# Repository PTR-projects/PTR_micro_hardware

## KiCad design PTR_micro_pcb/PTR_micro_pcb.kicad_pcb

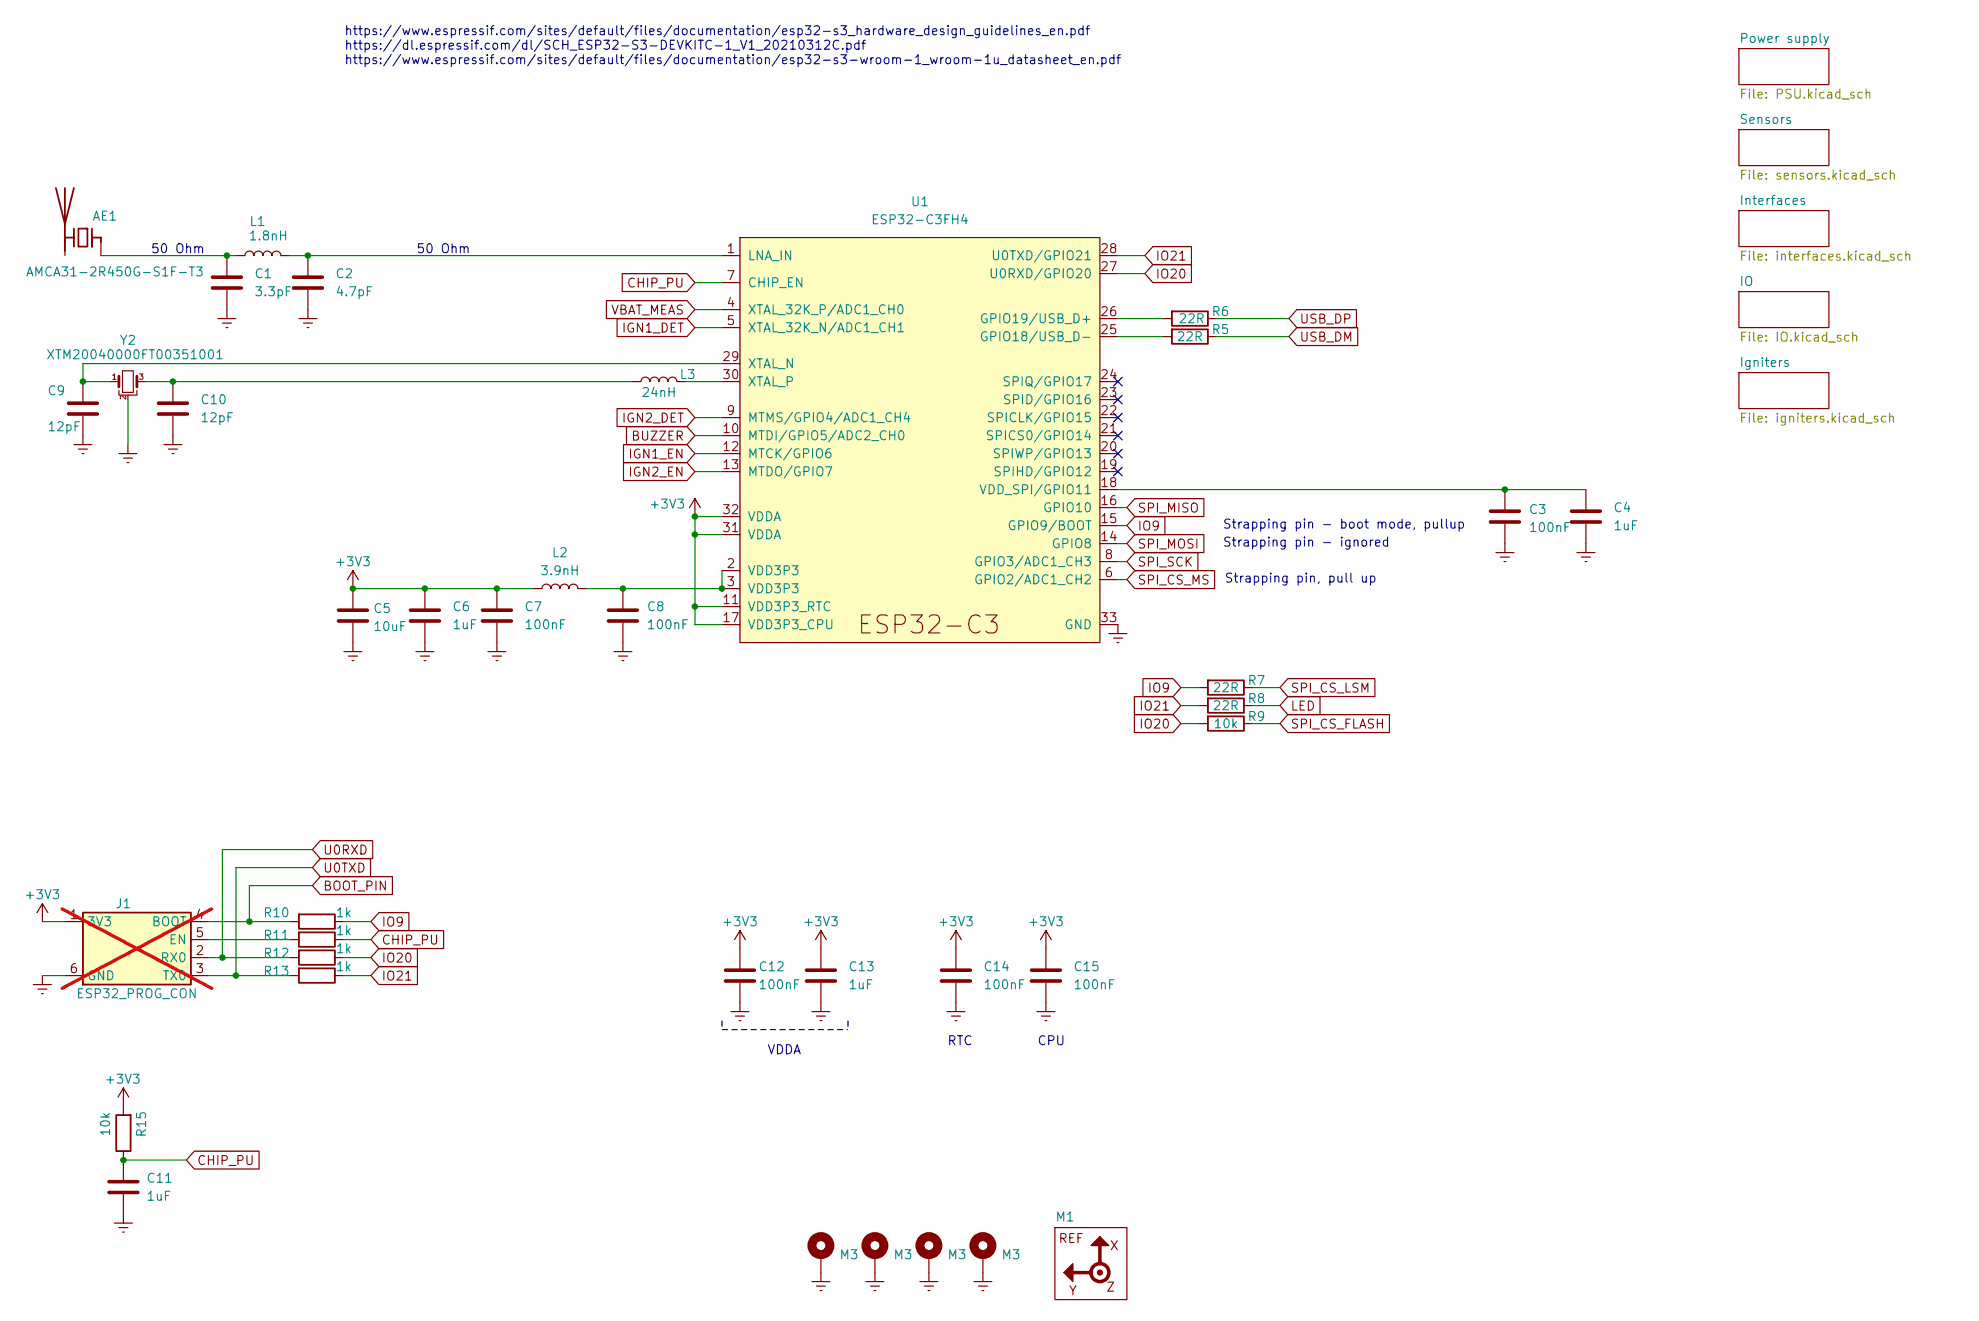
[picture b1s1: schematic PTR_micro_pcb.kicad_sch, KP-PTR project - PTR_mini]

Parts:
AE1: AMCA31-2R450G-S1F-T3
C1: 3.3pF; C_0402_1005Metric
C2: 4.7pF; C_0402_1005Metric
C3, C7, C8, C12, C14, C15: 100nF; C_0402_1005Metric
C4, C6, C11, C13: 1uF; C_0402_1005Metric
C5: 10uF; C_0603_1608Metric
C9, C10: 12pF; C_0402_1005Metric
H1, H2, H3, H4: M3; MountingHole_3.2mm_M3_DIN965_Pad
J1: ESP32_PROG_CON; PinHeader_1x06_P1.27mm_Vertical; not fitted
L1: 1.8nH; L_0402_1005Metric
L2: 3.9nH; L_0402_1005Metric
L3: 24nH; L_0402_1005Metric
M1: Reference_frame
R5, R6, R7, R8: 22R; R_0402_1005Metric
R9, R15: 10k; R_0402_1005Metric
R10, R11, R12, R13: 1k; R_0402_1005Metric
U1: ESP32-C3FH4; QFN-32-1EP_5x5mm_P0.5mm_EP3.45x3.45mm
Y2: XTM20040000FT00351001; Crystal_SMD_2016-4Pin_2.0x1.6mm

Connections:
+3V3: C5.1, C6.1, C7.1, C12.1, C13.1, C14.1, C15.1, J1.1 (3V3), L2.1, R15.2, U1.11 (VDD3P3_RTC), U1.17 (VDD3P3_CPU), U1.31 (VDDA), U1.32 (VDDA); also elsewhere on the board
BOOT_PIN: J1.4 (BOOT), R10.2
BUZZER: U1.10 (MTDI/GPIO5/ADC2_CH0); also elsewhere on the board
CHIP_PU: C11.2, R11.1, R15.1, U1.7 (CHIP_EN)
Earth: C1.2, C2.2, C3.2, C4.2, C5.2, C6.2, C7.2, C8.2, C9.1, C10.2, C11.1, C12.2, C13.2, C14.2, C15.2, H1.1 (1_1), H2.1 (1_1), H3.1 (1_1), H4.1 (1_1), J1.6 (GND), U1.33 (GND), Y2.2, Y2.4; also elsewhere on the board
IGN1_DET: U1.5 (XTAL_32K_N/ADC1_CH1); also elsewhere on the board
IGN1_EN: U1.12 (MTCK/GPIO6); also elsewhere on the board
IGN2_DET: U1.9 (MTMS/GPIO4/ADC1_CH4); also elsewhere on the board
IGN2_EN: U1.13 (MTDO/GPIO7); also elsewhere on the board
IO9: R7.2, R10.1, U1.15 (GPIO9/BOOT)
IO20: R9.2, R12.1, U1.27 (U0RXD/GPIO20)
IO21: R8.2, R13.1, U1.28 (U0TXD/GPIO21)
LED: R8.1; also elsewhere on the board
unnamed: AE1.1 (FEED_1), C1.1, L1.1
unnamed: C8.1, L2.2, U1.2 (VDD3P3), U1.3 (VDD3P3)
unnamed: C10.1, L3.1, Y2.3
unnamed: J1.5 (EN), R11.2
unnamed: R5.2, U1.25 (GPIO18/USB_D-)
unnamed: R6.2, U1.26 (GPIO19/USB_D+)
unnamed: C2.1, L1.2, U1.1 (LNA_IN)
unnamed: C3.1, C4.1, U1.18 (VDD_SPI/GPIO11)
unnamed: C9.2, U1.29 (XTAL_N), Y2.1
unnamed: L3.2, U1.30 (XTAL_P)
SPI_CS_FLASH: R9.1; also elsewhere on the board
SPI_CS_LSM: R7.1; also elsewhere on the board
SPI_CS_MS: U1.6 (GPIO2/ADC1_CH2); also elsewhere on the board
SPI_MISO: U1.16 (GPIO10); also elsewhere on the board
SPI_MOSI: U1.14 (GPIO8); also elsewhere on the board
SPI_SCK: U1.8 (GPIO3/ADC1_CH3); also elsewhere on the board
U0RXD: J1.2 (RX0), R12.2
U0TXD: J1.3 (TX0), R13.2
USB_DM: R5.1; also elsewhere on the board
USB_DP: R6.1; also elsewhere on the board
VBAT_MEAS: U1.4 (XTAL_32K_P/ADC1_CH0); also elsewhere on the board

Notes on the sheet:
Strapping pin - boot mode, pullup
Strapping pin, pull up
https://www.espressif.com/sites/default/files/documentation/esp32-s3_hardware_design_guidelines_en.pdf https://dl.espressif.com/dl/SCH_ESP32-S3-DEVKITC-1_V1_20210312C.pdf https://www.espressif.com/sites/default/files/documentation/esp32-s3-wroom-1_wroom-1u_datasheet_en.pdf
50 Ohm
VDDA
Strapping pin - ignored
CPU
RTC

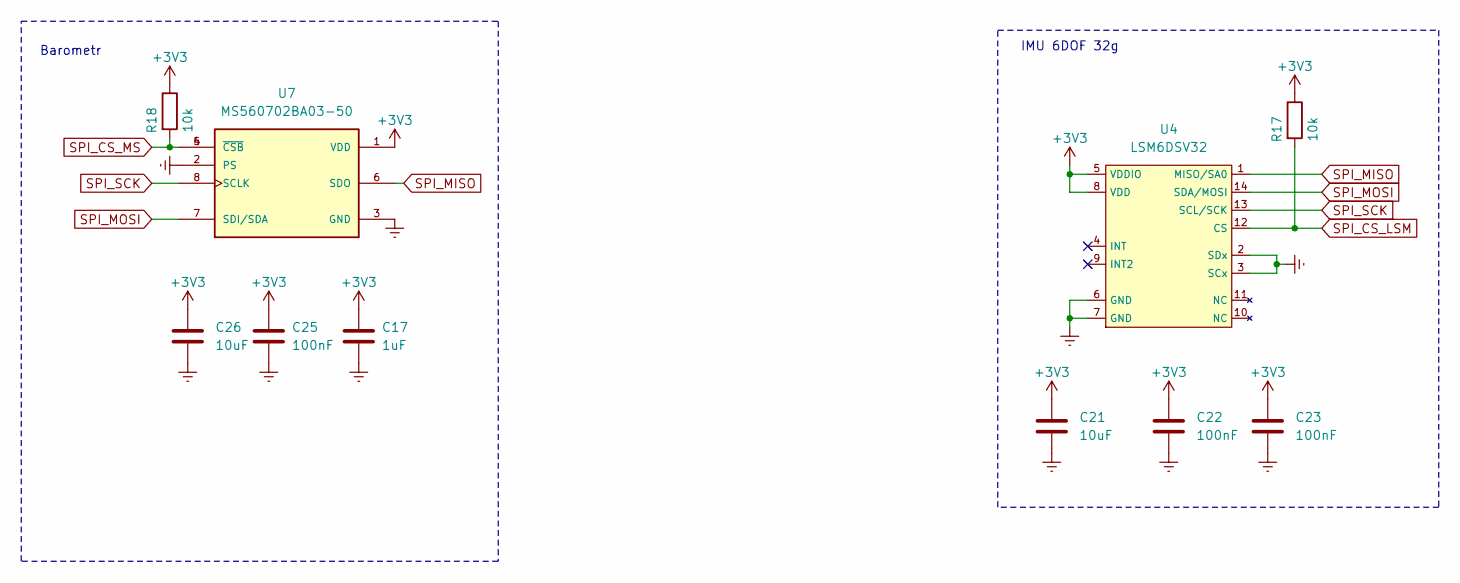
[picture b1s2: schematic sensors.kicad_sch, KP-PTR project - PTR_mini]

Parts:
C17: 1uF; C_0402_1005Metric
C21, C26: 10uF; C_0603_1608Metric
C22, C23, C25: 100nF; C_0402_1005Metric
R17, R18: 10k; R_0402_1005Metric
U4: LSM6DSV32; LSM6DSO32
U7: MS560702BA03-50; MS5607

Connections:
+3V3: C17.1, C21.1, C22.1, C23.1, C25.1, C26.1, R17.1, R18.1, U4.5 (VDDIO), U4.8 (VDD), U7.1 (VDD); also elsewhere on the board
Earth: C17.2, C21.2, C22.2, C23.2, C25.2, C26.2, U4.2 (SDx), U4.3 (SCx), U4.6 (GND), U4.7 (GND), U7.2 (PS), U7.3 (GND); also elsewhere on the board
SPI_CS_LSM: R17.2, U4.12 (CS); also elsewhere on the board
SPI_CS_MS: R18.2, U7.4 (~CSB), U7.5 (~CSB); also elsewhere on the board
SPI_MISO: U4.1 (MISO/SA0), U7.6 (SDO); also elsewhere on the board
SPI_MOSI: U4.14 (SDA/MOSI), U7.7 (SDI/SDA); also elsewhere on the board
SPI_SCK: U4.13 (SCL/SCK), U7.8 (SCLK); also elsewhere on the board

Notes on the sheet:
IMU 6DOF 32g
Barometr

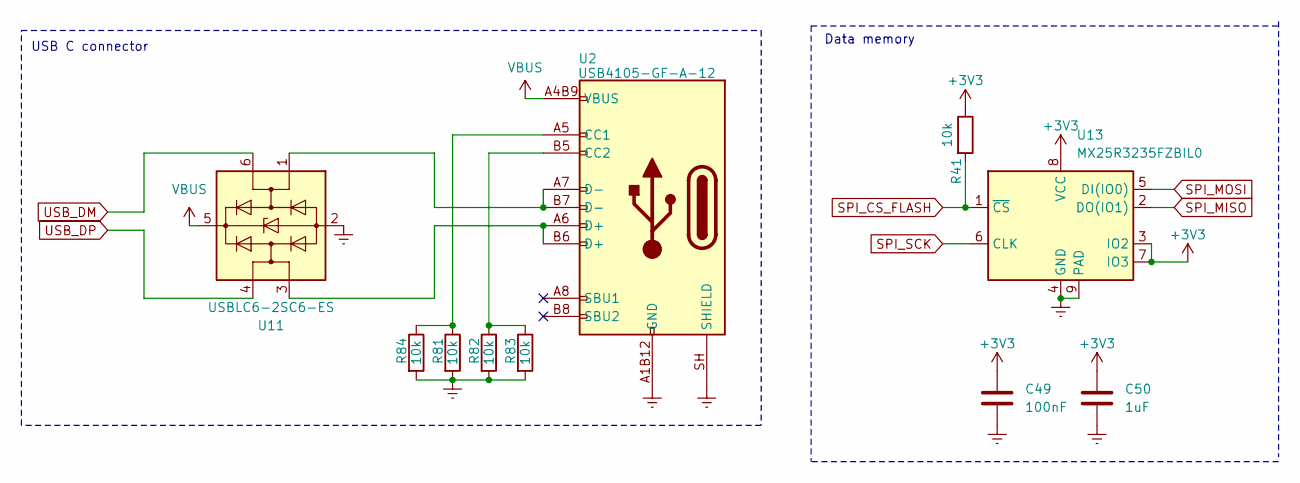
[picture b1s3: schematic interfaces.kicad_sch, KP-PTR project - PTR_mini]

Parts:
C49: 100nF; C_0402_1005Metric
C50: 1uF; C_0402_1005Metric
R41, R81, R82, R83, R84: 10k; R_0402_1005Metric
U2: USB4105-GF-A-12; USB_C_16P_SMD_USB4105-GF-A
U11: USBLC6-2SC6-ES; SOT-23-6
U13: MX25R3235FZBIL0; Winbond_USON-8-2EP_3x4mm_P0.8mm_EP0.2x0.8mm

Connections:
+3V3: C49.1, C50.1, R41.1, U13.3 (IO2), U13.7 (IO3), U13.8 (VCC); also elsewhere on the board
Earth: C49.2, C50.2, R81.2, R82.2, R83.2, R84.2, U2.A1B12 (GND), U2.B1A12 (GND), U2.SH (SHIELD), U11.2 (GND), U13.4 (GND), U13.9 (PAD); also elsewhere on the board
unnamed: R81.1, R84.1, U2.A5 (CC1)
unnamed: R82.1, R83.1, U2.B5 (CC2)
unnamed: U2.A7 (D-), U2.B7 (D-), U11.1 (I/O1)
unnamed: U2.A6 (D+), U2.B6 (D+), U11.3 (I/O2)
SPI_CS_FLASH: R41.2, U13.1 (~CS); also elsewhere on the board
SPI_MISO: U13.2 (DO(IO1)); also elsewhere on the board
SPI_MOSI: U13.5 (DI(IO0)); also elsewhere on the board
SPI_SCK: U13.6 (CLK); also elsewhere on the board
USB_DM: U11.6 (I/O1); also elsewhere on the board
USB_DP: U11.4 (I/O2); also elsewhere on the board
VBUS: U2.A4B9 (VBUS), U2.B4A9 (VBUS), U11.5 (VBUS); also elsewhere on the board

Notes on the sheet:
USB C connector
Data memory

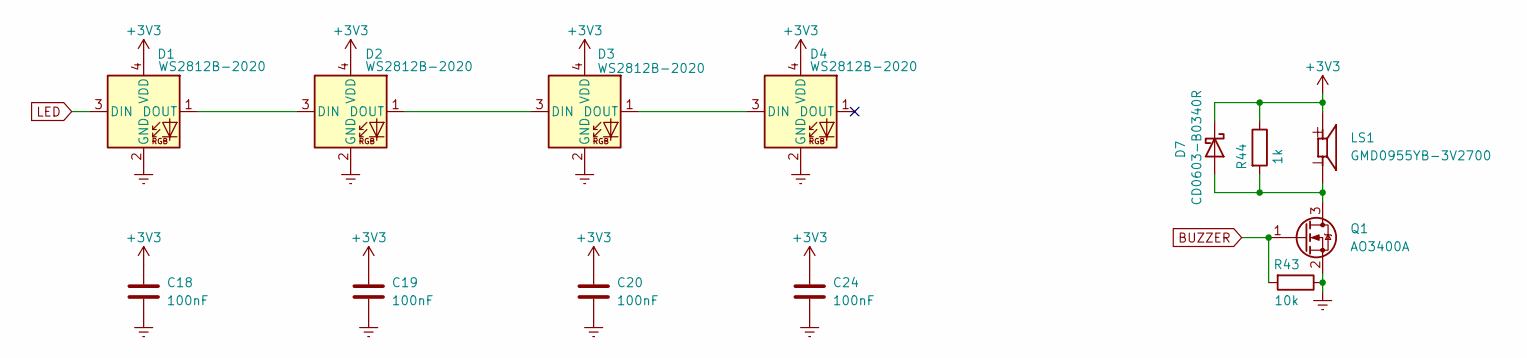
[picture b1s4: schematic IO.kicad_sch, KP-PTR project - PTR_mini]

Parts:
C18, C19, C20, C24: 100nF; C_0402_1005Metric
D1, D2, D3, D4: WS2812B-2020
D7: CD0603-B0340R; D_0603_1608Metric
LS1: GMD0955YB-3V2700; MagneticBuzzer_PUI_AT-0927-TT-6-R
Q1: AO3400A; SOT-23
R43: 10k; R_0402_1005Metric
R44: 1k; R_0402_1005Metric

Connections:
+3V3: C18.1, C19.1, C20.1, C24.1, D1.4 (VDD), D2.4 (VDD), D3.4 (VDD), D4.4 (VDD), D7.1 (K), LS1.1 (+), R44.1; also elsewhere on the board
BUZZER: Q1.1 (G), R43.2; also elsewhere on the board
Earth: C18.2, C19.2, C20.2, C24.2, D1.2 (GND), D2.2 (GND), D3.2 (GND), D4.2 (GND), Q1.2 (S), R43.1; also elsewhere on the board
LED: D1.3 (DIN); also elsewhere on the board
unnamed: D1.1 (DOUT), D2.3 (DIN)
unnamed: D2.1 (DOUT), D3.3 (DIN)
unnamed: D3.1 (DOUT), D4.3 (DIN)
unnamed: D7.2 (A), LS1.2 (-), Q1.3 (D), R44.2

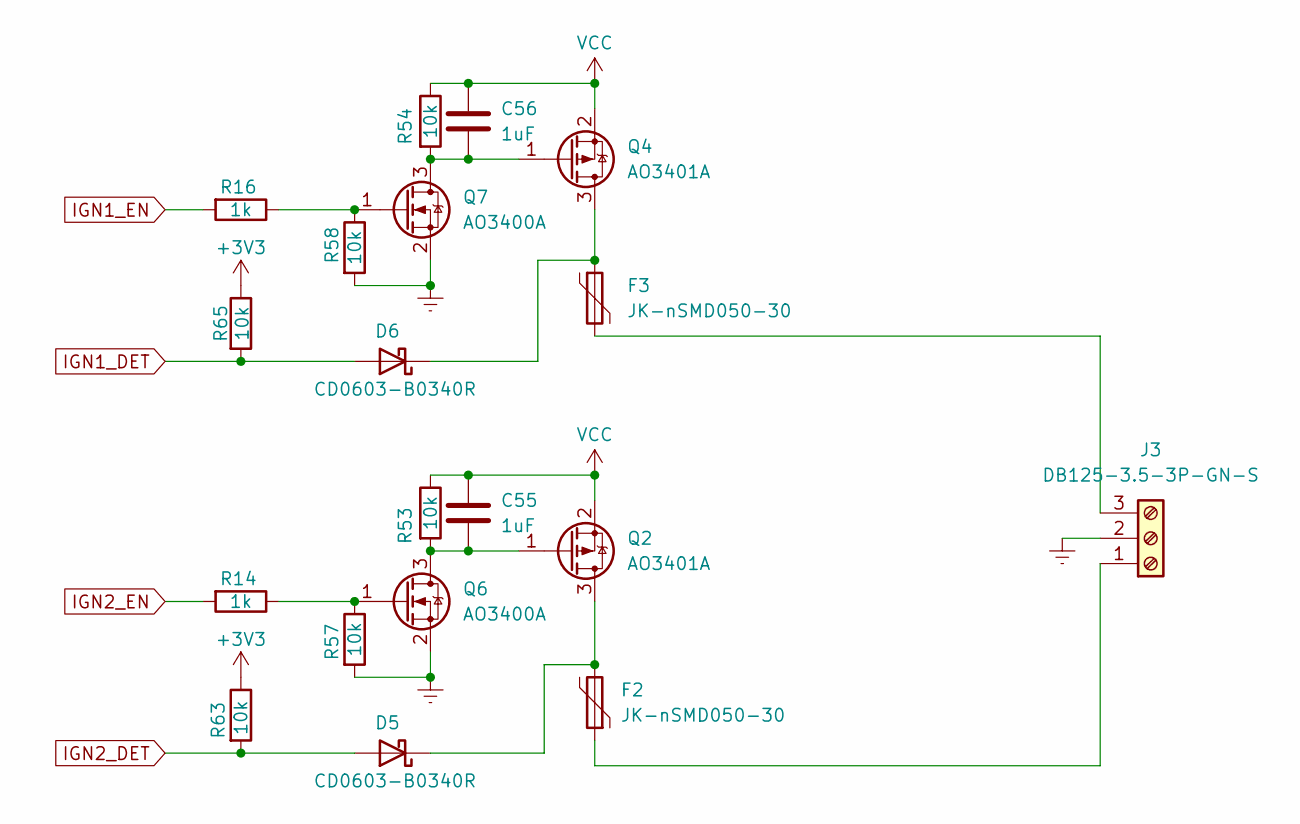
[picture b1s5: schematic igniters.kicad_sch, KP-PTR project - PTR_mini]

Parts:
C55, C56: 1uF; C_0402_1005Metric
D5, D6: CD0603-B0340R; D_0603_1608Metric
F2, F3: JK-nSMD050-30; Fuse_1206_3216Metric
J3: DB125-3.5-3P-GN-S; TerminalBlock_Phoenix_PT-1,5-3-3.5-H_1x03_P3.50mm_Horizontal
Q2, Q4: AO3401A; SOT-23
Q6, Q7: AO3400A; SOT-23
R14, R16: 1k; R_0402_1005Metric
R53, R54, R57, R58, R63, R65: 10k; R_0402_1005Metric

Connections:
+3V3: R63.1, R65.1; also elsewhere on the board
Earth: J3.2, Q6.2 (S), Q7.2 (S), R57.2, R58.2; also elsewhere on the board
IGN1_DET: D6.2 (A), R65.2; also elsewhere on the board
IGN1_EN: R16.2; also elsewhere on the board
IGN2_DET: D5.2 (A), R63.2; also elsewhere on the board
IGN2_EN: R14.2; also elsewhere on the board
unnamed: D5.1 (K), F2.2, Q2.3 (D)
unnamed: D6.1 (K), F3.1, Q4.3 (D)
unnamed: F2.1, J3.1
unnamed: F3.2, J3.3
unnamed: C55.2, Q2.1 (G), Q6.3 (D), R53.2
unnamed: C56.2, Q4.1 (G), Q7.3 (D), R54.2
unnamed: Q6.1 (G), R14.1, R57.1
unnamed: Q7.1 (G), R16.1, R58.1
VCC: C55.1, C56.1, Q2.2 (S), Q4.2 (S), R53.1, R54.1; also elsewhere on the board

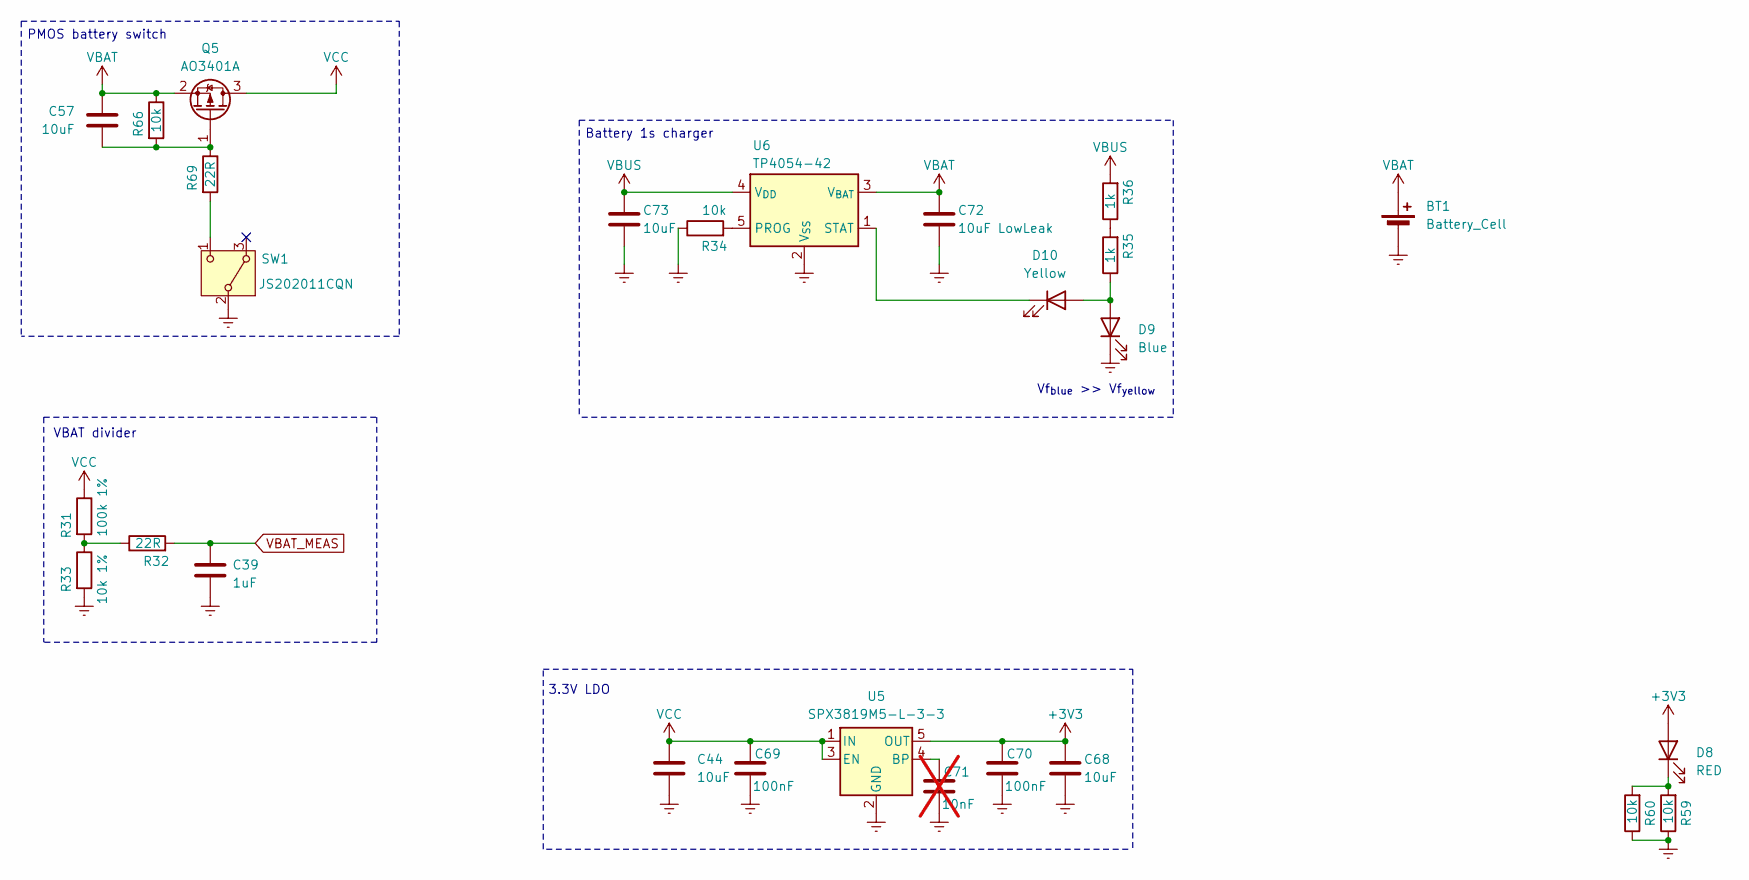
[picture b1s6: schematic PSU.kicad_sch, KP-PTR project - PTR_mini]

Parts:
BT1: Battery_Cell; LiPol_90mAh
C39: 1uF; C_0402_1005Metric
C44, C57, C68, C73: 10uF; C_0603_1608Metric
C69, C70: 100nF; C_0402_1005Metric
C71: 10nF; C_0402_1005Metric; not fitted
C72: 10uF LowLeak; C_0603_1608Metric
D8: RED; LED_0603_1608Metric
D9: Blue; LED_0603_1608Metric
D10: Yellow; LED_0603_1608Metric
Q5: AO3401A; SOT-23
R31: 100k 1%; R_0402_1005Metric
R32, R69: 22R; R_0402_1005Metric
R33: 10k 1%; R_0402_1005Metric
R34, R59, R60, R66: 10k; R_0402_1005Metric
R35, R36: 1k; R_0402_1005Metric
SW1: JS202011CQN
U5: SPX3819M5-L-3-3; SOT-23-5
U6: TP4054-42; SOT-23-5

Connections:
+3V3: C68.1, C70.1, D8.2 (A), U5.5 (OUT); also elsewhere on the board
Earth: BT1.2 (-), C39.2, C44.2, C68.2, C69.2, C70.2, C71.2, C72.2, C73.2, D9.1 (K), R33.2, R34.1, R59.1, R60.1, SW1.2 (B), U5.2 (GND), U6.2 (V_{SS}); also elsewhere on the board
unnamed: D8.1 (K), R59.2, R60.2
unnamed: D9.2 (A), D10.2 (A), R35.1
unnamed: D10.1 (K), U6.1 (STAT)
unnamed: C57.2, Q5.1 (G), R66.2, R69.1
unnamed: R31.2, R32.1, R33.1
unnamed: R35.2, R36.1
unnamed: R69.2, SW1.1 (C)
unnamed: C71.1, U5.4 (BP)
unnamed: R34.2, U6.5 (PROG)
VBAT: BT1.1 (+), C57.1, C72.1, Q5.2 (S), R66.1, U6.3 (V_{BAT})
VBAT_MEAS: C39.1, R32.2; also elsewhere on the board
VBUS: C73.1, R36.2, U6.4 (V_{DD}); also elsewhere on the board
VCC: C44.1, C69.1, Q5.3 (D), R31.1, U5.1 (IN), U5.3 (EN); also elsewhere on the board

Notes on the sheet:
Vf_{blue} >> Vf_{yellow}
PMOS battery switch
VBAT divider
Battery 1s charger
3.3V LDO

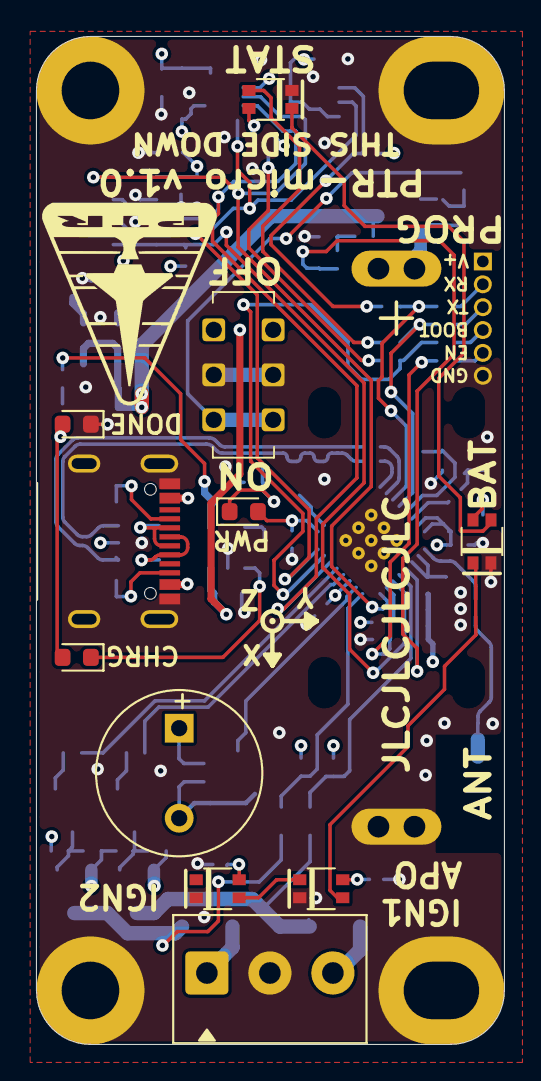
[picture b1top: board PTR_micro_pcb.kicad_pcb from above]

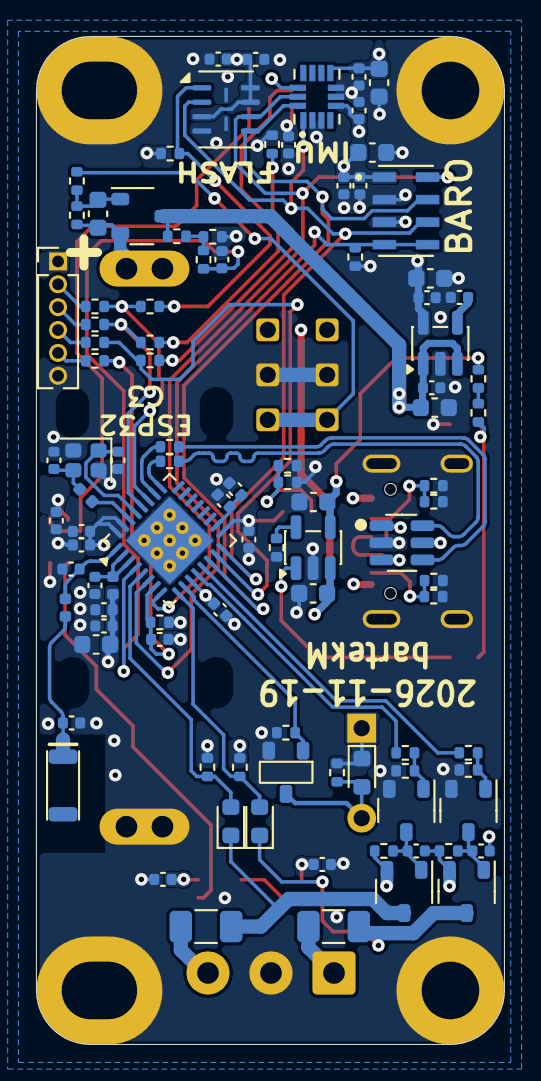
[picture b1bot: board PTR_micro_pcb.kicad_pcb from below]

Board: 4 copper layers, 26.0 x 56.0 mm, 116 parts (99 on the bottom side), 62 nets.

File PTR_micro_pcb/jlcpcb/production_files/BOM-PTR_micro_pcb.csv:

Comment,Designator,Footprint,LCSC,Quantity
1.8nH,L1,L_0402_1005Metric,C77107,1
100k 1%,R31,R_0402_1005Metric,C25741,1
100nF,"C12,C14,C15,C18,C19,C20,C22,C23,C24,C25,C3,C49,C69,C7,C70,C8",C_0402_1005Metric,C1525,16
10k,"R15,R17,R18,R34,R41,R43,R53,R54,R57,R58,R59,R60,R63,R65,R66,R81,R82,R83,R84,R9",R_0402_1005Metric,C25744,20
10k 1%,R33,R_0402_1005Metric,C25744,1
10uF,"C21,C26,C44,C5,C57,C68,C73",C_0603_1608Metric,C96446,7
10uF LowLeak,C72,C_0603_1608Metric,C96446,1
12pF,"C10,C9",C_0402_1005Metric,C1547,2
1k,"R10,R11,R12,R13,R14,R16,R35,R36,R44",R_0402_1005Metric,C11702,9
1uF,"C11,C13,C17,C39,C4,C50,C55,C56,C6",C_0402_1005Metric,C52923,9
22R,"R32,R5,R6,R69,R7,R8",R_0402_1005Metric,C25092,6
24nH,L3,L_0402_1005Metric,C74301,1
3.3pF,C1,C_0402_1005Metric,C5448815,1
3.9nH,L2,L_0402_1005Metric,C77109,1
4.7pF,C2,C_0402_1005Metric,C1569,1
AMCA31-2R450G-S1F-T3,AE1,AMCA31-2R450G-S1F-T3,C3283994,1
AO3400A,"Q1,Q6,Q7",SOT-23,C20917,3
AO3401A,"Q2,Q4,Q5",SOT-23,C15127,3
Blue,D9,LED_0603_1608Metric,C51933294,1
CD0603-B0340R,"D5,D6,D7",D_0603_1608Metric,C3759853,3
DB125-3.5-3P-GN-S,J3,"TerminalBlock_Phoenix_PT-1,5-3-3.5-H_1x03_P3.50mm_Horizontal",C466971,1
ESP32-C3FH4,U1,QFN-32-1EP_5x5mm_P0.5mm_EP3.45x3.45mm,C2858491,1
GMD0955YB-3V2700,LS1,MagneticBuzzer_PUI_AT-0927-TT-6-R,C252933,1
JK-nSMD050-30,"F2,F3",Fuse_1206_3216Metric,C720075,2
JS202011CQN,SW1,JS202011CQN,C221663,1
LSM6DSV32,U4,LSM6DSO32,C22461202,1
MS560702BA03-50,U7,MS5607,C97627,1
MX25R3235FZBIL0,U13,Winbond_USON-8-2EP_3x4mm_P0.8mm_EP0.2x0.8mm,C6242573,1
RED,D8,LED_0603_1608Metric,C965799,1
SPX3819M5-L-3-3,U5,SOT-23-5,C9055,1
TP4054-42,U6,SOT-23-5,C32574,1
USB4105-GF-A-12,U2,USB_C_16P_SMD_USB4105-GF-A,C5184243,1
USBLC6-2SC6-ES,U11,SOT-23-6,C5180249,1
WS2812B-2020,"D1,D2,D3,D4",WS2812B-2020,C52917434,4
XTM20040000FT00351001,Y2,Crystal_SMD_2016-4Pin_2.0x1.6mm,C37635335,1
Yellow,D10,LED_0603_1608Metric,C965808,1
